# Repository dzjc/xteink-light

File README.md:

Kicad project files and Freecad 3D model for minimal reading light for the xteink x4

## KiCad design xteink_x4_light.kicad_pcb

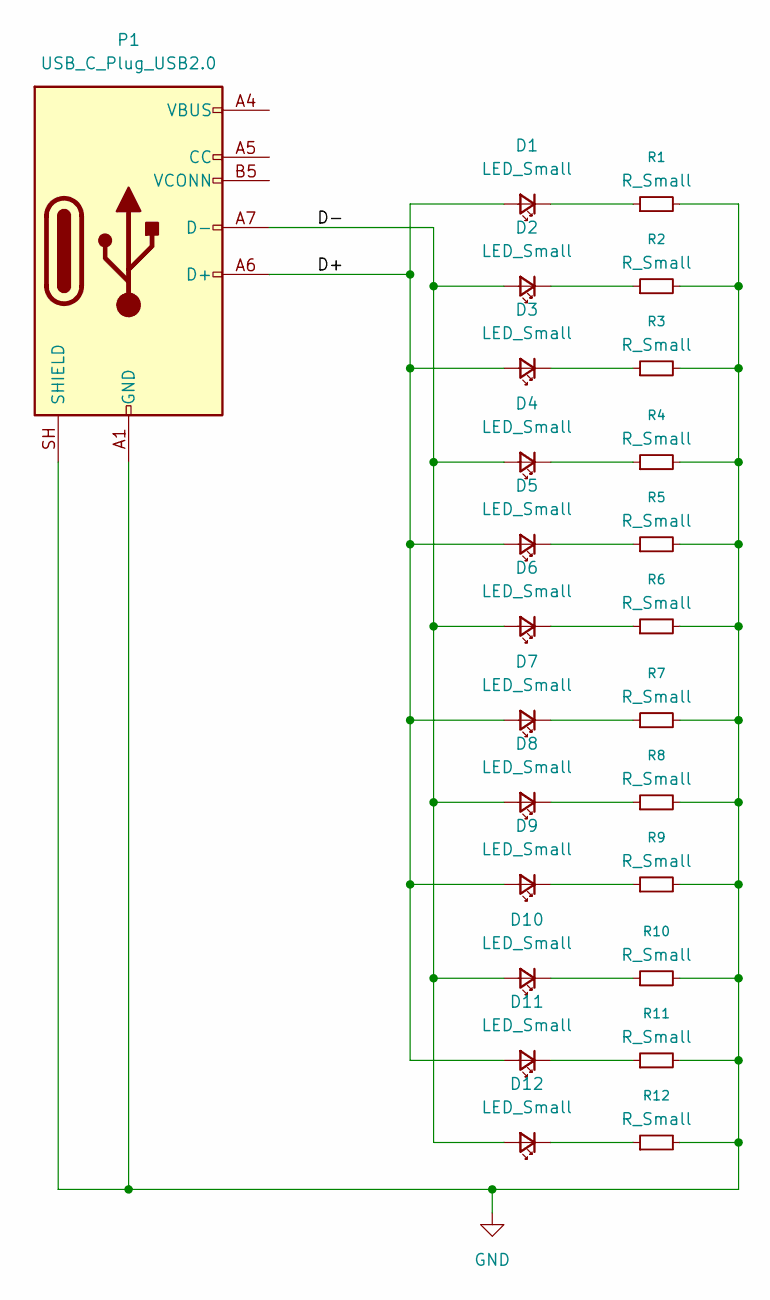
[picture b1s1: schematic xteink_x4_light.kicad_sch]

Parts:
D1, D2, D3, D4, D5, D6, D7, D8, D9, D10, D11, D12: LED_Small; LED_0402_1005Metric
P1: USB_C_Plug_USB2.0; USB_C_Plug_ShenzhenJingTuoJin_918-118A2021Y40002_Vertical
R1, R2, R3, R4, R5, R6, R7, R8, R9, R10, R11, R12: R_Small; R_0402_1005Metric

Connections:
/D+: D1.2 (A), D3.2 (A), D5.2 (A), D7.2 (A), D9.2 (A), D11.2 (A), P1.A6 (D+)
/D-: D2.2 (A), D4.2 (A), D6.2 (A), D8.2 (A), D10.2 (A), D12.2 (A), P1.A7 (D-)
GND: P1.A1 (GND), P1.A12 (GND), P1.B1 (GND), P1.B12 (GND), P1.SH (SHIELD), R1.2, R2.2, R3.2, R4.2, R5.2, R6.2, R7.2, R8.2, R9.2, R10.2, R11.2, R12.2
unnamed: D1.1 (K), R1.1
unnamed: D2.1 (K), R2.1
unnamed: D3.1 (K), R3.1
unnamed: D4.1 (K), R4.1
unnamed: D5.1 (K), R5.1
unnamed: D6.1 (K), R6.1
unnamed: D7.1 (K), R7.1
unnamed: D8.1 (K), R8.1
unnamed: D9.1 (K), R9.1
unnamed: D10.1 (K), R10.1
unnamed: D11.1 (K), R11.1
unnamed: D12.1 (K), R12.1
unnamed: P1.A4 (VBUS), P1.A9 (VBUS), P1.B4 (VBUS), P1.B9 (VBUS)

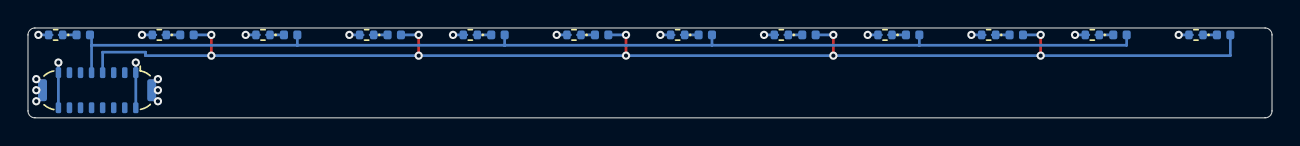
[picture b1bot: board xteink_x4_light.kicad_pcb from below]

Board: 2 copper layers, 90.0 x 6.5 mm, 25 parts (25 on the bottom side), 16 nets.

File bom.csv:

"Id";"Designator";"Footprint";"Quantity";"Designation";"Supplier and ref";
1;"D1, D1, D1, D1, D1, D2, D2, D2, D2, D2, D3, D3, D3, D3, D3, D4, D4, D4, D4, D4, D5, D5, D5, D5, D5, D6, D6, D6, D6, D6, D7, D7, D7, D7, D7, D8, D8, D8, D8, D8, D9, D9, D9, D9, D9, D10, D10, D10, D10, D10, D11, D11, D11, D11, D11, D12, D12, D12, D12, D12";"LED_0402_1005Metric";60;"LED_Small";;;
2;"P1, P1, P1, P1, P1";"USB_C_Plug_ShenzhenJingTuoJin_918-118A2021Y40002_Vertical";5;"USB_C_Plug_USB2.0";;;
3;"R1, R1, R1, R1, R1, R2, R2, R2, R2, R2, R3, R3, R3, R3, R3, R4, R4, R4, R4, R4, R5, R5, R5, R5, R5, R6, R6, R6, R6, R6, R7, R7, R7, R7, R7, R8, R8, R8, R8, R8, R9, R9, R9, R9, R9, R10, R10, R10, R10, R10, R11, R11, R11, R11, R11, R12, R12, R12, R12, R12";"R_01005_0402Metric";60;"R_Small";;;
